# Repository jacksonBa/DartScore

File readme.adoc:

= DartScore, branch: DartScorePython3

== Counting scores in dart with image recognition

This branch is forked from DartScoreEngine branch and it is ported to Python3.
It is also simplified a lot when it comes to modules and setups. This is the current 'master'- branch
and the only DartScore branch currently maintained and I will probably remove the others in the future.

The purpose of this project is to make something that also can be used by others without
too much effort. I put up the information I think is needed for this, but if you miss something, give me a hint and I
will update with that as well.

Currently the project is in 'MVP' (minimum viable product) status wich means that it has a minimum of
functionallity but can be used for real. The supported functionallity is:

* Mounting state to help setting up the cam
* Calibration state to calibrate and transform the image stream from one cam and saving/reading calibration matrix from file
* Playstate supporting one player and a simple algorithm for counting scores for each set of darts but not very accurate
right now.
* All states has a hardcoded gui that is presented on a screen with 1680x1050 resolution

But it works (sort of...) !

image:Docs/20200105_185252.jpg[DartScore installation]

== Improvements that will come in future updates (and the current priority):
This is the current plan for this project. The aim is to be able to distribute a project that can be used by others
as soon as possible (the MVP) and then continue with the development of features from there.

* Performace optimisation (main issue right now)
* A better algorithm for counting the scores (main issue right now)
* Support for IO: buttons, leds, temperature-monitor and fans
* Configurable gui (To make it easier for others to use)
* Support for real and configurable gametypes like 301, 501 etc (To be able to use it for real)
* Scoreboard in the cloud (Better incitament for others to use)
* Support for 2 players (To be able to use it for real)
* Support for 2 cams (To further improve the score calculation)
* Saving game stats and be able to continue a game (Nice to have)
* ... more to come...

**Prerequisites:**
------------------
* Python 3.x, PyGame and OpenCv 3.4.x
* Headunit: Raspberry Pi 4 2GB, Rasbian Buster full (includes Python3 and Python-game)
* Network cam, i.e. Raspberry Pi 2 or 3 with a raspicam and motioneyeos configured as a fast networked cam

== Install open cv and dependencies:
These where the packages I had to install to get opencv to work:

- pip3 install opencv-python
- sudo apt-get install libatlas-base-dev
- sudo apt-get install libjasper-dev
- sudo apt-get install libqtgui4
- sudo apt-get install python3-pyqt5
- sudo apt install libqt4-test

image:Docs/20191217_154805.jpg[DartScore screen]

== How to use it:

* First you need to install all the prerequisites and have a dartboard available :-)
The dartboard need a good and even lighting, preferable a 'light-box'.
* Next step is to setup the networkdéd camera and install the software. I use a raspberry pi with
a raspi-cam and motioneyeos.
* When the cam is installed and the project is 'cloned' you need to
change the pathes and settings in DartScoreEngineConfig.py to fit your installation,
including the cam-url for the image stream.
* Now its time to mount the camera to have a good view of the dartboard. To help with this, navigate to the
StateLoops directory and run
`sudo python3 CamMountingLoop.py` When done press any key to quit. _*TIP*_: I use the zoom-function in the
fast netcam setup
to be able to have the cam on a distance but still fill the frame with the board as much as possible.
* When the cam is mounted and has a correct view of the dartboard its time to calibrate for the first time. Do
this with `sudo python3 CamCalibrateLoop.py` When done press any key to quit.
* Hopefully the calibration succeeded otherwise you have to change threshold and filter values in the
calibration loop components. This will be more described and configurable in future releases of DartScore.
* When calibrated the first time its possible to just run `sudo python3 Main.py` from the SW directory and the
game starts for real.

(The procedure will be simplified in the future but since I do not have any IO at this point the mount and cal
states needs to be run manually for the first time)

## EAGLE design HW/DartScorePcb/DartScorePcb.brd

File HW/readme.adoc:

= Dartscore hardware

This readme file describes the DartScore hardware like board, cams, brackets, lightning, moutning details etc etc...

The board:
----------
I use a lightbox for the board to get even lighting conditions.
The 'frame' of the lightox is made of solid oak wood panels (from www.ess-enn.se) cut to the right size and with a
milled 'track'
for the led-tape (standard 12V with 5mm squared leds and c/c  15mm).
The led-strip is located at a distance of 70mm off, from the board-surface
and the inside of the box is 500x500 mm.

image:../Docs/dartboardlightbox.jpg[the lightingbox]

image:../Docs/20200106_105349.jpg[Closeup]

Closeup of the mounted led tape.

The Cam(s):
-----------
I use a raspberry pi 3 with a raspicam and the motioneyeos (https://github.com/ccrisan/motioneyeos)  in fast networked cam setup.
Currently one cam is used but the project will be prepared for two in the future.

image:Netcam_front.jpg[One of the netcams]

One of the cameras

image:../Docs/bracket-bottom.jpg[Camera bracket]

The 3d printed camera bracket. Cambracket 1/2.stl are the 3D printer models for this bracket.
I use standard M3 machine-screws to put it together.

In the future there will probably be a complete 3d printable enclosure with bracket for the cams, that fit is purpose
better then the one used today.

The PCB:
--------
In the 'eagle' directory is  a circuit board designed to use with a raspberry pi 4 as the
main computing device in the DartScore project.

The first version of the pcb is like an array of relays, designed with connectors for switches and leds and also for
the control of 2 fans,
one for the CPU and one for the 'box'.  In my project I use 'arcade-switches' from Adafruit and they need 5V as supply for
the builtin leds. Therefore all outputs are 'switched' with mosfets (the 'relays').
The same goes for the fans which are 12V
supplied (I use standard PC fans).

The PCB is available from here: https://aisler.net/p/PMFAHSJW

In the future the PCB will probably be more sofisticated, like one 12V inpout that drives everything including the
Pi itself.

image:DartScorePcb_v1.jpg[The pcb]

Physical installation:
----------------------

image:../Docs/20200105_154200.jpg[The PCB in action..]

Note that the PCB is mounted with the connectors on the ouside of the Pi-enclosure, otherwise the cooling-fan
shouldn't work. Th sockets to the left are used for connectiong the archade buttons and the socket to the right for
12V from a transformer, supplying the lightbox and the fans

The DartScore station:
----------------------
image:../Docs/20200105_185252.jpg[The station...]

The lightbox with the Adafruit archade switches mounted between the box and the screen.

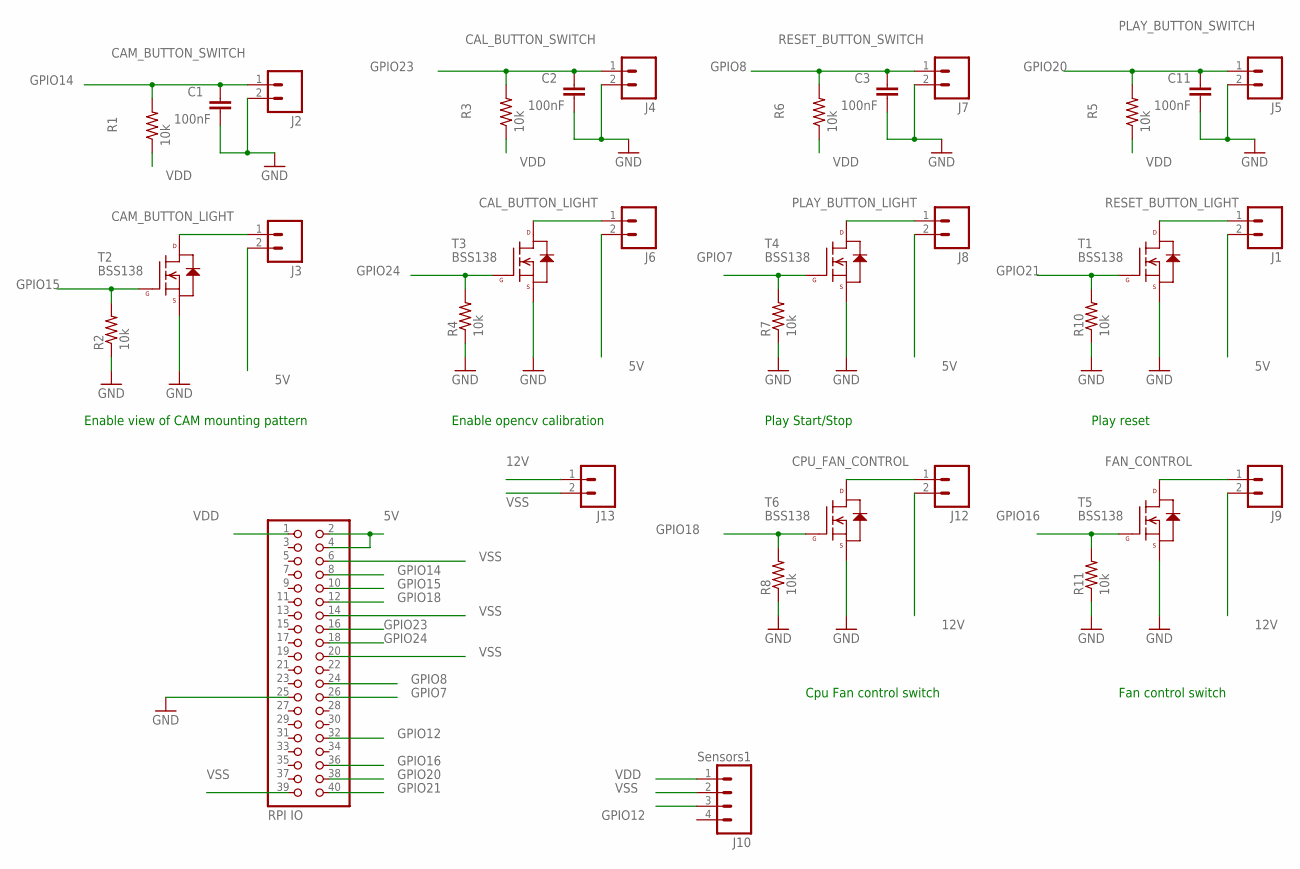
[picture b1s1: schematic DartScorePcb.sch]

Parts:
C1, C2, C3, C11: 100nF; 0805
J1: RESET_BUTTON_LIGHT; 1X02
J2: CAM_BUTTON_SWITCH; 1X02
J3: CAM_BUTTON_LIGHT; 1X02
J4: CAL_BUTTON_SWITCH; 1X02
J5: PLAY_BUTTON_SWITCH; 1X02
J6: CAL_BUTTON_LIGHT; 1X02
J7: RESET_BUTTON_SWITCH; 1X02
J8: PLAY_BUTTON_LIGHT; 1X02
J9: FAN_CONTROL; 1X02
J10: Sensors1; 1X04
J12, J13: CPU_FAN_CONTROL; 1X02
JP2: RPI IO; 2X20
R1, R2, R3, R4, R5, R6, R7, R8, R10, R11: 10k; 0805
T1, T2, T3, T4, T5, T6: BSS138; SOT23-3

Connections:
5V: J1.2, J3.2, J6.2, J8.2, JP2.2, JP2.4
12V: J9.2, J12.2, J13.1
GPIO7: JP2.26, R7.2, T4.1 (G)
GPIO8: C3.1, J7.1, JP2.24, R6.2
GPIO12: J10.3, JP2.32
GPIO14: C1.1, J2.1, JP2.8, R1.2
GPIO15: JP2.10, R2.2, T2.1 (G)
GPIO16: JP2.36, R11.2, T5.1 (G)
GPIO18: JP2.12, R8.2, T6.1 (G)
GPIO20: C11.1, J5.1, JP2.38, R5.2
GPIO21: JP2.40, R10.2, T1.1 (G)
GPIO23: C2.1, J4.1, JP2.16, R3.2
GPIO24: JP2.18, R4.2, T3.1 (G)
unnamed: J9.1, T5.3 (D)
unnamed: J1.1, T1.3 (D)
unnamed: J12.1, T6.3 (D)
unnamed: J3.1, T2.3 (D)
unnamed: J6.1, T3.3 (D)
unnamed: J8.1, T4.3 (D)
VDD: J10.1, JP2.1, R1.1, R3.1, R5.1, R6.1
VSS: C1.2, C2.2, C3.2, C11.2, J2.2, J4.2, J5.2, J7.2, J10.2, J13.2, JP2.6, JP2.14, JP2.20, JP2.25, JP2.39, R2.1, R4.1, R7.1, R8.1, R10.1, R11.1, T1.2 (S), T2.2 (S), T3.2 (S), T4.2 (S), T5.2 (S), T6.2 (S)

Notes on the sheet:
Play reset
Enable view of CAM mounting pattern
Enable opencv calibration
Play Start/Stop
Fan control switch
Cpu Fan control switch

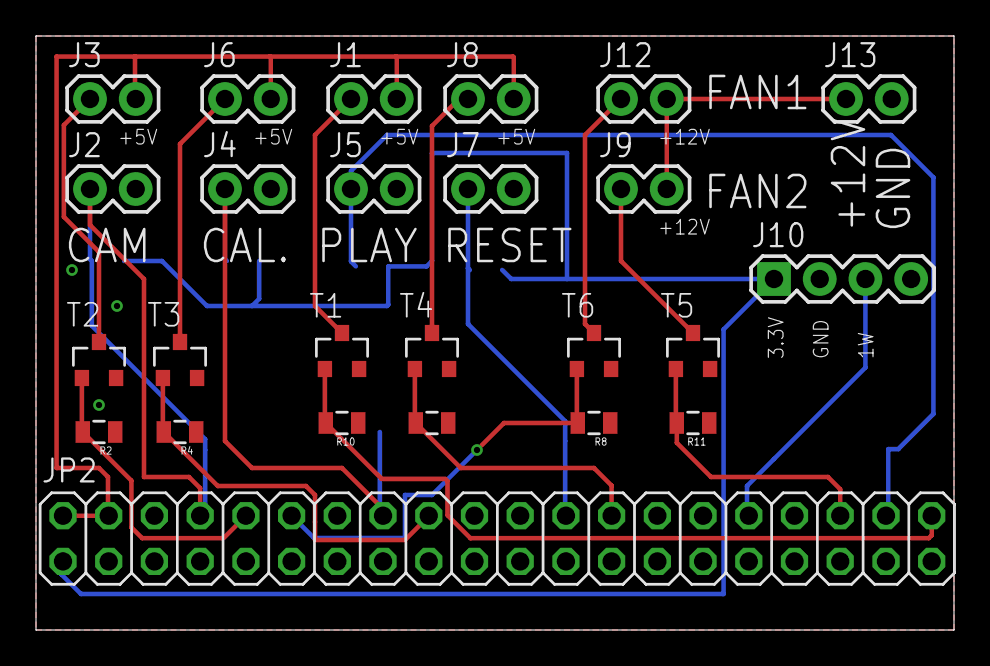
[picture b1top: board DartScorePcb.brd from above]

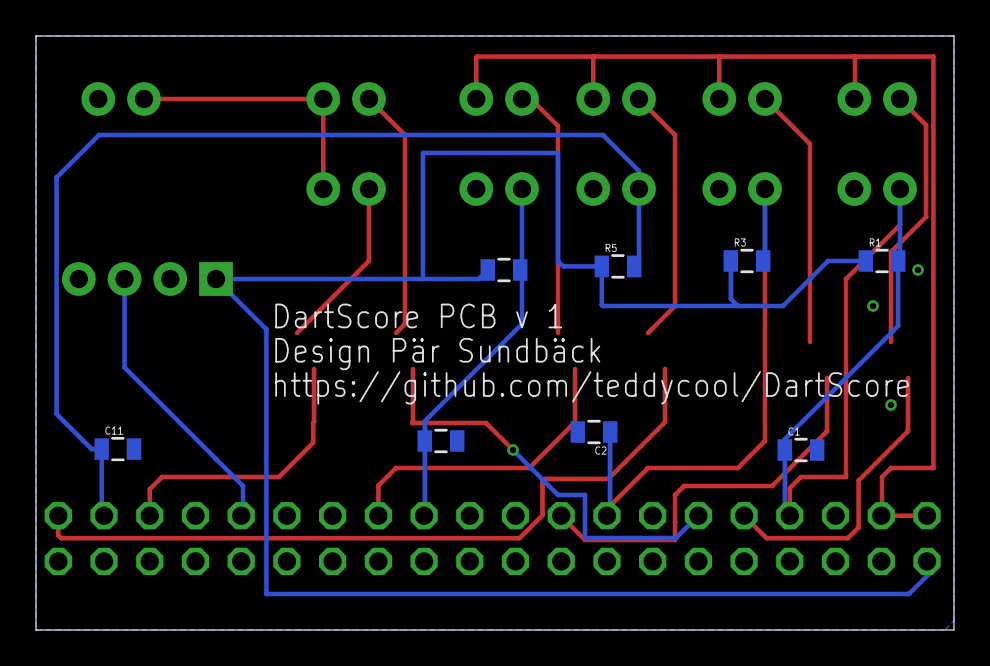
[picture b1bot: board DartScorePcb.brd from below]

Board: 2 copper layers, 51.0 x 33.0 mm, 33 parts (8 on the bottom side), 21 nets.

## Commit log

2020-03-05 Virtual environment setup and code refactored slightly

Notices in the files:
parts and their libraries:
SparkFun-Passives: Licensing: Creative Commons ShareAlike 4.0 International - https://creativecommons.org/licenses/by-sa/4.0
